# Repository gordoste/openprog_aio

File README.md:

# openprog_aio
All-in-one variant of Alberto Maccioni's wonderful Openprog PIC/AVR programmer (http://openprog.altervista.org/).

## Benefits

For low-voltage programming, the big advantage of this programmer over something like the MPLAB Snap is that it can provide power to the target device, and all of the surrounding circuitry (bypass caps, etc.) is built onto the board. You just plug in a device and program it.

The programmer is also fully capable of high-voltage programming. This is essential if you need to program an older device, and it also means you can use the MCLR pin as an extra I/O, which can be very handy on low-pin-count devices.

This version is aimed at allowing you to get started for the lowest cost and without making your own PCBs. Therefore, the following changes have been made from the original project:

* No adapter boards - just one board, making it cheaper to order from PCB fabrication shops.
* Board is still reasonable size at 158x100mm - approx twice the size of the original project's main board
* Designed to be easily hand-soldered, with 1206 size SMD components. The trickiest thing to solder is the USB socket. You shouldn't need any special equipment if you have clear vision and good lighting - just 0.3mm solder, flux paste and de-soldering braid. NOTE: If you are hand-soldering, it is recommended to use a USB Mini-B socket - see [Part List](#part-list).
* Documentation is on the board, including clear delineation between 5V/3.3V
* Ability to use ZIF sockets for all 20/28 pin sockets if desired.
* PROG button can be used even if device is programmed in low-voltage mode (previously it was attached to RE3/#MCLR)
* ICSP inputs match the MPLAB Snap pinout (different from PICKit).

Please note that the 40-pin Wide DIP sockets have been removed as those devices are rarely used now and took up too much room. If you want to program those devices, you can easily connect the ICSP output to a breadboard.

## Before you start

You need temporary access to a PIC programmer to construct this project. If you don't have a friend with a programmer, the MPLAB Snap is the cheapest commercial option.

## Schematic

The schematic is [here](schematic.pdf).

## Firmware

The original firmware uses unsupported tooling (MCC). I have ported the firmware to MPLAB X and it is available at <https://github.com/gordoste/openprog>. All testing of this board is conducted using this firmware, and testing status of the board/firmware combo can be found at the firmware repository.

## Part List

You can copy and paste [this part list](bom/partlist.txt) into Mouser's BOM tool to order the passive components and semiconductors. In addition to those, you will need the following which are best ordered from AliExpress or similar:
1. IC sockets. You may wish to only populate the sockets you use. Here is a list of all of the sockets:
   | Socket ID | Socket pin count | Device family | Voltage | Device pin count | Can be ZIF? |
   | ----------|------------------|---------------|---------|------------------|-------------|
   | A | 28 | PIC12/16/18 | 3.3V | 28 | Y  |
   | B | 20 | PIC12/16/18 | 3.3V | 8/14/18/20 | Y |
   | C | 28 | PIC24/30/33 | 3.3V | 20/28 | Y |
   | D | 20 | AVR Tiny x61A | 5V | 20 | Y |
   | E | 28 | AVR | 5V | 20/28 | Y |
   | F | 28 | PIC30 | 5V | 18/28 | Y |
   | G | 28 | PIC12/16/18 | 5V | 28 | Y |
   | H | 20 | PIC12/16/18 | 5V | 8/14/16/20 | Y |
   | - | 18 | PIC24-33 | 3.3V | 14/18 | N |
   | - | 8  | SPI Flash | 3.3V | 8 | N |
   | - | 8  | SPI Flash | 5V | 8 | N |
   | - | 8  | uWire Flash | 5V | 8 | N |
   | - | 8  | I2C/UNIO Flash | 5V | 8 | N |
   | - | 8  | PIC 10F20x | 5V | 8 | N |
   | - | 8  | AVR Tiny | 5V | 8 | N |
   | - | 14 | AVR Tiny | 5V | 14 | N |
2. 2.54mm (0.1") pitch pin headers. 3 x 2-pin, 3 x 5-pin, 2 x 4-pin and 1 x 3-pin (all straight). Optionally, you can use a 90-degree header for the 5-pin MPLAB Snap connector.
3. one 6x6mm SMD push button for the PROG button (two if you choose to fit the RESET button)
4. USB socket - either thru-hole Mini-B (I got some from AliExpress which worked fine) or SMD Micro-B (GCT part # USB3076-30-A) (this has fine-pitch pins and is not easy to hand-solder).

## Construction Notes

Download the [ZIP file](https://github.com/gordoste/openprog_aio/releases/download/v1.0b/Openprog_All-in-one_1.0b.zip) containing the PCB gerber files and submit it to your favourite production house.

You can use [this interactive BOM](ibom.html) to assist in placing parts.

Assuming you are hand-soldering, solder the parts in the following order:
1. Back side: Transistors, diodes, resistors, capacitors, regulator
2. Front side: Transistors, diodes, resistors, LEDs, ceramic capacitors, inductor, PIC18F25K50, button(s), electrolytic cap, USB socket, pin headers.

Be careful to only apply a small amount of solder when soldering the USB socket, as it is very easy to create a bridge. Don't panic if you do - turn your soldering iron up a bit hotter than normal, apply a liberal amount of flux and then use desolder braid to try to get rid of __all__ of the solder from the bridged pins. Once it's cleaned up, try again with less solder.

After you've soldered everything, download the HEX file from the [firmware repository](https://github.com/gordoste/openprog) and program it onto the PIC. The marked "MPLAB_SNAP" connector matches the pinout of the Snap (as shown below) - if you're using a PICKit then you will need to utilise jumper wires to connect the programmer.

Assuming you've done everything right, when you plug it into your PC, it should show up as "Open Programmer" and the openprog GUI should be able to talk to it. I recommend using the command line "op" tool with the "-HWtest" option to run through basic checks before actually trying to program anything. See the [openprog webpage](http://openprog.altervista.org/) for more information.

## Usage Notes

### Programming 3.3V I2C EEPROMs

The original project did not provide a socket for this, and I have not yet added one. You can use the SPI@3.3V pin header and connect the following:
|Header pin|Device pin|
|----------|----------|
|GND|GND (4)|
|SCL|SCL (6)|
|MISO|SDA (5)|

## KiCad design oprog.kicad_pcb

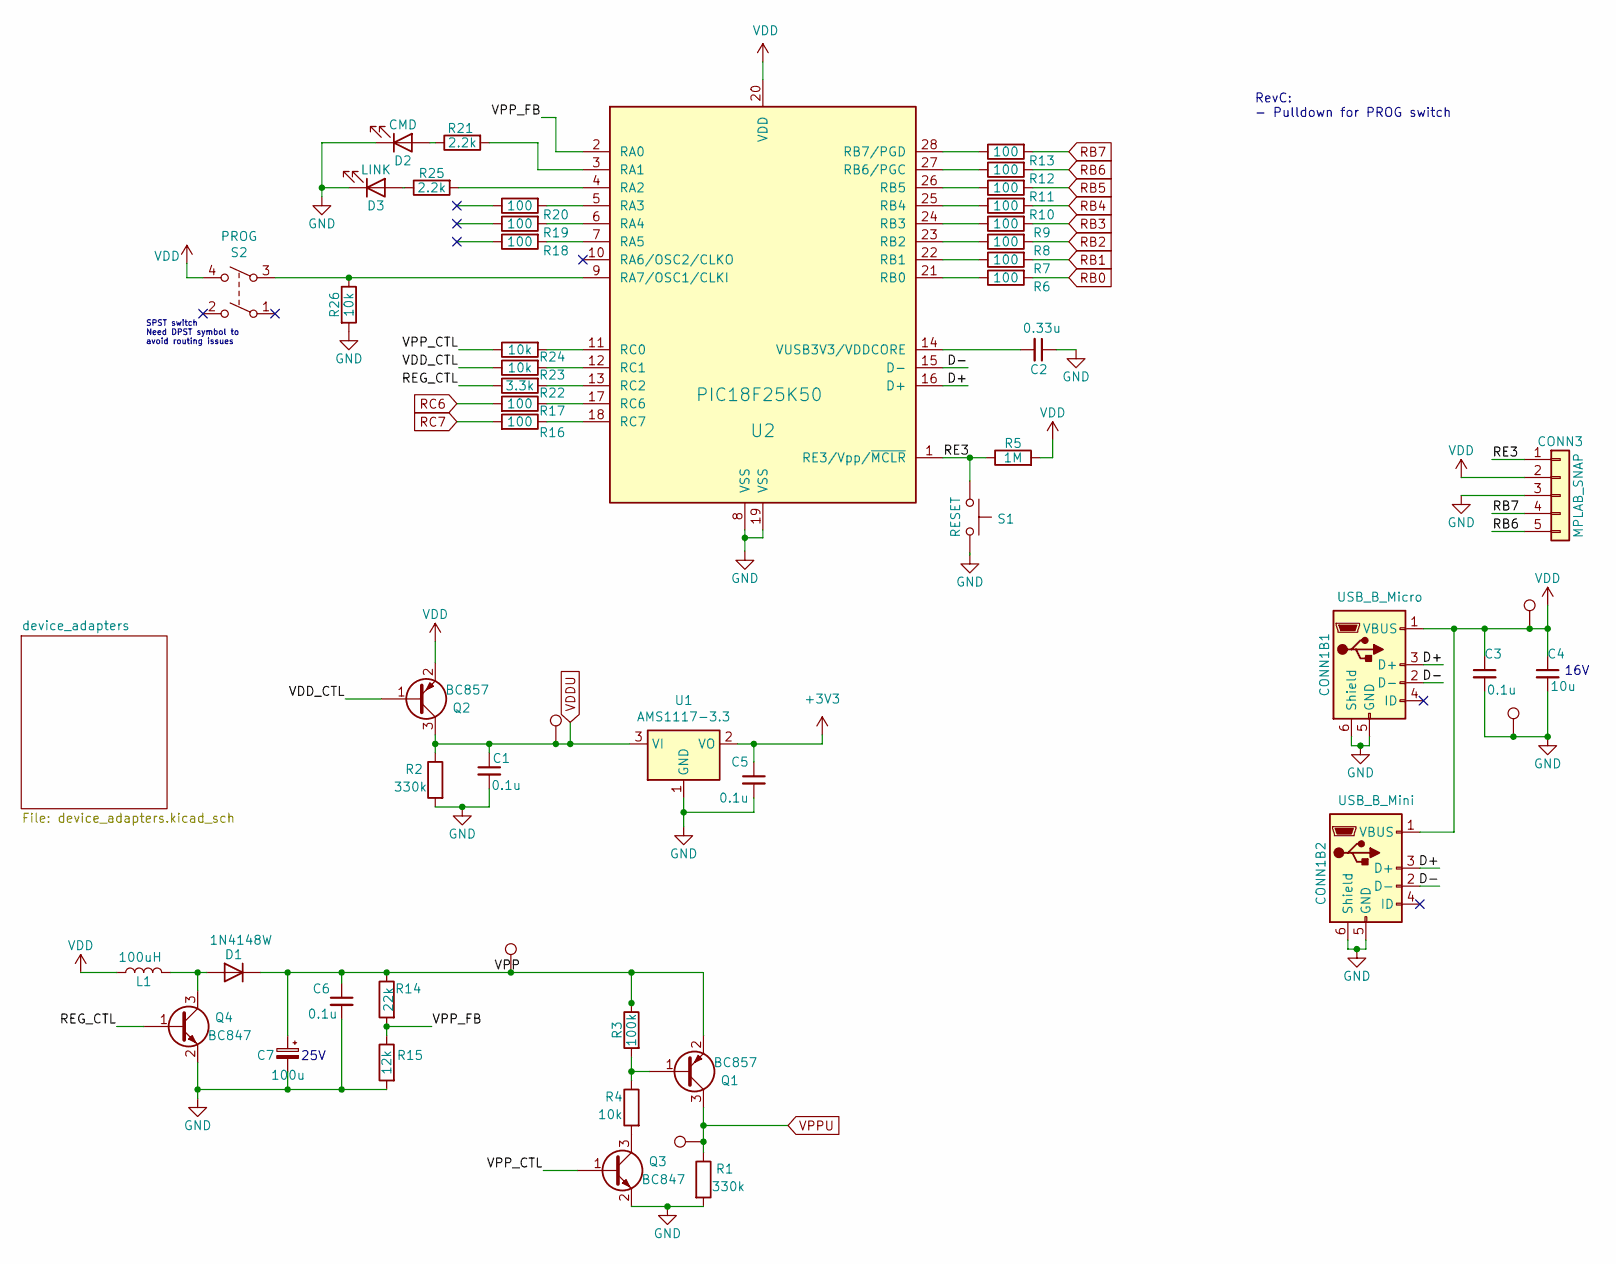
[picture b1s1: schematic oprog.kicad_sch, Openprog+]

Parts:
C1, C3, C5, C6: 0.1u; C_1206_3216Metric_Pad1.33x1.80mm_HandSolder
C2: 0.33u; C_1206_3216Metric_Pad1.33x1.80mm_HandSolder
C4: 10u; C_1206_3216Metric_Pad1.33x1.80mm_HandSolder
C7: 100u; CP_Elec_6.3x5.7
CONN1B1: USB_B_Micro; USB_Micro-B_GCT_USB3076-30-A
CONN1B2: USB_B_Mini; USB_Mini_Type_B_Aliexpress
CONN3: MPLAB_SNAP; PinHeader_1x05_P2.54mm_Vertical
D1: 1N4148W; D_SOD-123
D2: CMD; LED_1206_3216Metric_Pad1.42x1.75mm_HandSolder
D3: LINK; LED_1206_3216Metric_Pad1.42x1.75mm_HandSolder
L1: 100uH; L_1210_3225Metric_Pad1.42x2.65mm_HandSolder
Q1, Q2: BC857; SOT-23
Q3, Q4: BC847; SOT-23
R1, R2: 330k; R_1206_3216Metric_Pad1.30x1.75mm_HandSolder
R3: 100k; R_1206_3216Metric_Pad1.30x1.75mm_HandSolder
R4, R23, R24, R26: 10k; R_1206_3216Metric_Pad1.30x1.75mm_HandSolder
R5: 1M; R_1206_3216Metric_Pad1.30x1.75mm_HandSolder
R6, R7, R8, R9, R10, R11, R12, R13, R16, R17, R18, R19, R20: 100; R_1206_3216Metric_Pad1.30x1.75mm_HandSolder
R14: 22k; R_1206_3216Metric_Pad1.30x1.75mm_HandSolder
R15: 12k; R_1206_3216Metric_Pad1.30x1.75mm_HandSolder
R21, R25: 2.2k; R_1206_3216Metric_Pad1.30x1.75mm_HandSolder
R22: 3.3k; R_1206_3216Metric_Pad1.30x1.75mm_HandSolder
S1: RESET; SW_Push_1P1T_NO_6x6mm_2pads
S2: PROG; SW_Push_1P1T_NO_6x6mm_4pads
TP1: VPPU; TestPoint_THTPad_D1.0mm_Drill0.5mm
TP2: GND; TestPoint_THTPad_D1.0mm_Drill0.5mm
TP3: VDD; TestPoint_THTPad_D1.0mm_Drill0.5mm
TP7: VPP; TestPoint_THTPad_D1.0mm_Drill0.5mm
TP8: VDDU; TestPoint_THTPad_D1.0mm_Drill0.5mm
U1: AMS1117-3.3; SOT-223-3_TabPin2
U2: PIC18F25K50; SOIC-28W_7.5x17.9mm_P1.27mm

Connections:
+3V3: C5.1, U1.2 (VO); also elsewhere on the board
/D+: CONN1B1.3 (D+), CONN1B2.3 (D+), U2.16 (D+)
/D-: CONN1B1.2 (D-), CONN1B2.2 (D-), U2.15 (D-)
/RE3: CONN3.1, R5.1, S1.2, U2.1 (RE3/Vpp/~MCLR)
/REG_CTL: Q4.1 (B), R22.1
/VDD_CTL: Q2.1 (B), R23.1
/VPP: C6.1, C7.1, D1.1 (K), Q1.2 (E), R3.1, R14.1, TP7.1
/VPP_CTL: Q3.1 (B), R24.1
/VPP_FB: R14.2, R15.1, U2.2 (RA0)
GND: C1.2, C2.1, C3.2, C4.2, C5.2, C6.2, C7.2, CONN1B1.5 (GND), CONN1B1.6 (Shield), CONN1B2.5 (GND), CONN1B2.6 (Shield), CONN3.3, D2.1 (K), D3.1 (K), Q3.2 (E), Q4.2 (E), R1.2, R2.2, R15.2, R26.2, S1.1, TP2.1, U1.1 (GND), U2.8 (VSS), U2.19 (VSS); also elsewhere on the board
unnamed: D1.2 (A), L1.1, Q4.3 (C)
unnamed: D2.2 (A), R21.1
unnamed: D3.2 (A), R25.1
unnamed: Q1.1 (B), R3.2, R4.1
unnamed: Q3.3 (C), R4.2
unnamed: R21.2, U2.3 (RA1)
unnamed: R25.2, U2.4 (RA2)
unnamed: R20.2, U2.5 (RA3)
unnamed: R19.2, U2.6 (RA4)
unnamed: R18.2, U2.7 (RA5)
unnamed: R26.1, S2.3, U2.9 (RA7/OSC1/CLKI)
unnamed: R6.1, U2.21 (RB0)
unnamed: R7.1, U2.22 (RB1)
unnamed: R8.1, U2.23 (RB2)
unnamed: R9.1, U2.24 (RB3)
unnamed: R10.1, U2.25 (RB4)
unnamed: R11.1, U2.26 (RB5)
unnamed: R12.1, U2.27 (RB6/PGC)
unnamed: R13.1, U2.28 (RB7/PGD)
unnamed: R24.2, U2.11 (RC0)
unnamed: R23.2, U2.12 (RC1)
unnamed: R22.2, U2.13 (RC2)
unnamed: R17.1, U2.17 (RC6)
unnamed: R16.1, U2.18 (RC7)
unnamed: C2.2, U2.14 (VUSB3V3/VDDCORE)
RB0: R6.2; also elsewhere on the board
RB1: R7.2; also elsewhere on the board
RB2: R8.2
RB3: R9.2; also elsewhere on the board
RB4: R10.2; also elsewhere on the board
RB5: R11.2; also elsewhere on the board
RB6: CONN3.5, R12.2; also elsewhere on the board
RB7: CONN3.4, R13.2; also elsewhere on the board
RC6: R17.2; also elsewhere on the board
RC7: R16.2; also elsewhere on the board
VDD: C3.1, C4.1, CONN1B1.1 (VBUS), CONN1B2.1 (VBUS), CONN3.2, L1.2, Q2.2 (E), R5.2, S2.4, TP3.1, U2.20 (VDD)
VDDU: C1.1, Q2.3 (C), R2.1, TP8.1, U1.3 (VI); also elsewhere on the board
VPPU: Q1.3 (C), R1.1, TP1.1; also elsewhere on the board

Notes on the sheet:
RevC: - Pulldown for PROG switch
SPST switch Need DPST symbol to avoid routing issues
16V
25V

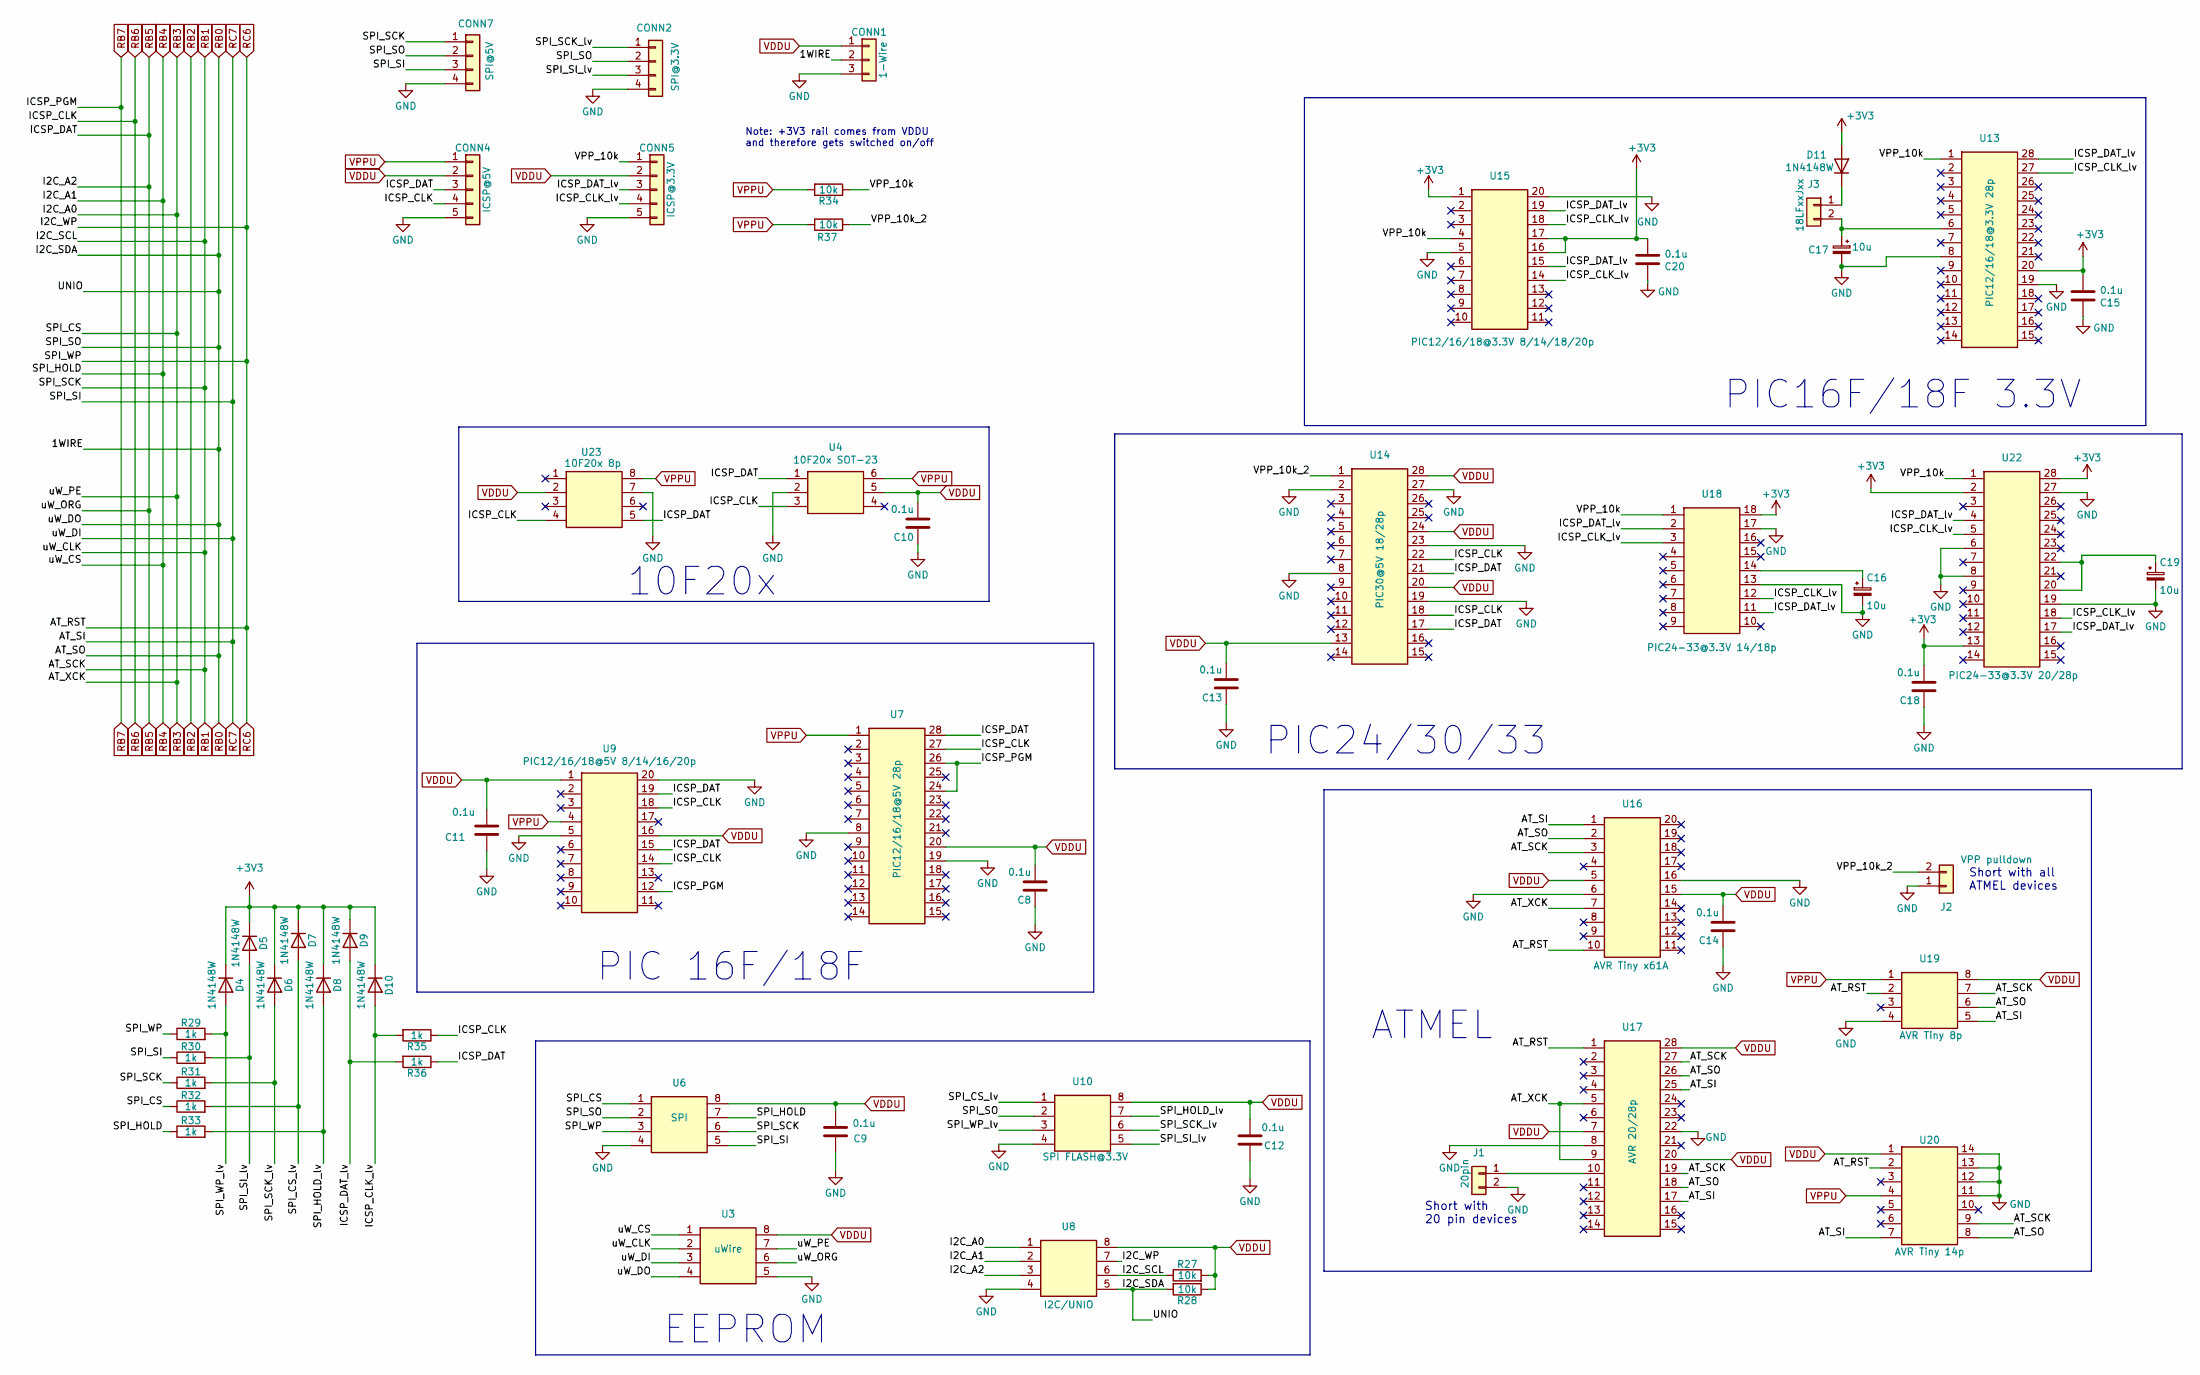
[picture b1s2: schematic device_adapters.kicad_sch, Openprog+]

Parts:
C8, C9, C10, C11, C12, C13, C14, C15, C18, C20: 0.1u; C_1206_3216Metric_Pad1.33x1.80mm_HandSolder
C16, C17, C19: 10u; C_1206_3216Metric_Pad1.33x1.80mm_HandSolder
CONN1: 1-Wire; PinHeader_1x03_P2.54mm_Vertical
CONN2: SPI@3.3V; PinHeader_1x04_P2.54mm_Vertical
CONN4: ICSP@5V; PinHeader_1x05_P2.54mm_Vertical
CONN5: ICSP@3.3V; PinHeader_1x05_P2.54mm_Vertical
CONN7: SPI@5V; PinHeader_1x04_P2.54mm_Vertical
D4, D5, D6, D7, D8, D9, D10, D11: 1N4148W; D_SOD-123
J1: 20pin; PinHeader_1x02_P2.54mm_Vertical
J2: VPP pulldown; PinHeader_1x02_P2.54mm_Vertical
J3: 18LFxxJxx; PinHeader_1x02_P2.54mm_Vertical
R27, R28, R34, R37: 10k; R_1206_3216Metric_Pad1.30x1.75mm_HandSolder
R29, R30, R31, R32, R33, R35, R36: 1k; R_1206_3216Metric_Pad1.30x1.75mm_HandSolder
U3: uWire; DIP-8_W7.62mm_Socket
U4: 10F20x SOT-23; SOT-23-6_Handsoldering
U6: SPI; DIP-8_W7.62mm_Socket
U7: PIC12/16/18@5V 28p; ZIFSocket_28p_W7.62mm
U8: I2C/UNIO; DIP-8_W7.62mm_Socket
U9: PIC12/16/18@5V 8/14/16/20p; ZIFSocket_20p_W7.62mm
U10: SPI FLASH@3.3V; DIP-8_W7.62mm_Socket
U13: PIC12/16/18@3.3V 28p; ZIFSocket_28p_W7.62mm
U14: PIC30@5V 18/28p; ZIFSocket_28p_W7.62mm
U15: PIC12/16/18@3.3V 8/14/18/20p; ZIFSocket_20p_W7.62mm
U16: AVR Tiny x61A; ZIFSocket_20p_W7.62mm
U17: AVR 20/28p; ZIFSocket_28p_W7.62mm
U18: PIC24-33@3.3V 14/18p; DIP-18_W7.62mm_Socket
U19: AVR Tiny 8p; DIP-8_W7.62mm_Socket
U20: AVR Tiny 14p; DIP-14_W7.62mm_Socket
U22: PIC24-33@3.3V 20/28p; ZIFSocket_28p_W7.62mm
U23: 10F20x 8p; DIP-8_W7.62mm_Socket

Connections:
+3V3: C15.2, C18.2, C20.2, D4.1 (K), D5.1 (K), D6.1 (K), D7.1 (K), D8.1 (K), D9.1 (K), D10.1 (K), D11.2 (A), U13.20, U15.1, U15.16, U15.17, U18.18, U22.2, U22.13, U22.28; also elsewhere on the board
/device_adapters/ICSP_CLK_lv: CONN5.4, D10.2 (A), R35.2, U13.27, U15.14, U15.18, U18.3, U18.12, U22.5, U22.18
/device_adapters/ICSP_DAT_lv: CONN5.3, D9.2 (A), R36.2, U13.28, U15.15, U15.19, U18.2, U18.11, U22.4, U22.17
/device_adapters/SPI_CS_lv: D7.2 (A), R32.2, U10.1
/device_adapters/SPI_HOLD_lv: D8.2 (A), R33.2, U10.7
/device_adapters/SPI_SCK_lv: CONN2.1, D6.2 (A), R31.2, U10.6
/device_adapters/SPI_SI_lv: CONN2.3, D5.2 (A), R30.2, U10.5
/device_adapters/SPI_WP_lv: D4.2 (A), R29.2, U10.3
/device_adapters/VPP_10k: CONN5.1, R34.1, U13.1, U15.4, U18.1, U22.1
/device_adapters/VPP_10k_2: J2.2, R37.2, U14.1
GND: C8.1, C9.1, C10.1, C11.1, C12.1, C13.1, C14.1, C15.1, C16.2, C17.2, C18.1, C19.2, C20.1, CONN1.3, CONN2.4, CONN4.5, CONN5.5, CONN7.4, J1.2, J2.1, U3.5, U4.2, U6.4, U7.8, U7.19, U8.4, U9.5, U9.20, U10.4, U13.8, U13.19, U14.2, U14.8, U14.19, U14.23, U14.27, U15.5, U15.20, U16.6, U16.16, U17.8, U17.22, U18.13, U18.17, U19.4, U20.11, U20.12, U20.13, U20.14, U22.6, U22.8, U22.19, U22.27, U23.7; also elsewhere on the board
unnamed: C16.1, U18.14
unnamed: C19.1, U22.20, U22.22
unnamed: D11.1 (K), J3.1
unnamed: J1.1, U17.10
unnamed: C17.1, J3.2, U13.6
RB0: CONN1.2, CONN2.2, CONN7.2, R28.2, U3.4, U6.2, U8.5, U10.2, U16.2, U17.18, U17.26, U19.6, U20.8; also elsewhere on the board
RB1: CONN7.1, R27.1, R31.1, U3.2, U6.6, U8.6, U16.3, U17.19, U17.27, U19.7, U20.9; also elsewhere on the board
RB3: R32.1, U3.7, U6.1, U8.1, U16.7, U17.5, U17.9; also elsewhere on the board
RB4: R33.1, U3.1, U6.7, U8.2; also elsewhere on the board
RB5: CONN4.3, R36.1, U3.6, U4.1, U7.28, U8.3, U9.15, U9.19, U14.17, U14.21, U23.5; also elsewhere on the board
RB6: CONN4.4, R35.1, U4.3, U7.27, U9.14, U9.18, U14.18, U14.22, U23.4; also elsewhere on the board
RB7: U7.24, U7.26, U9.12; also elsewhere on the board
RC6: R29.1, U6.3, U8.7, U16.10, U17.1, U19.2, U20.2; also elsewhere on the board
RC7: CONN7.3, R30.1, U3.3, U6.5, U16.1, U17.17, U17.25, U19.5, U20.7; also elsewhere on the board
VDDU: C8.2, C9.2, C10.2, C11.2, C12.2, C13.2, C14.2, CONN1.1, CONN4.2, CONN5.2, R27.2, R28.1, U3.8, U4.5, U6.8, U7.20, U8.8, U9.1, U9.16, U10.8, U14.13, U14.20, U14.24, U14.28, U16.5, U16.15, U17.7, U17.20, U17.28, U19.8, U20.1, U23.2; also elsewhere on the board
VPPU: CONN4.1, R34.2, R37.1, U4.6, U7.1, U9.4, U19.1, U20.4, U23.8; also elsewhere on the board

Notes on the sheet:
Short with all ATMEL devices
Note: +3V3 rail comes from VDDU and therefore gets switched on/off
PIC16F/18F 3.3V
10F20x
EEPROM
Short with 20 pin devices
PIC24/30/33
PIC 16F/18F
ATMEL

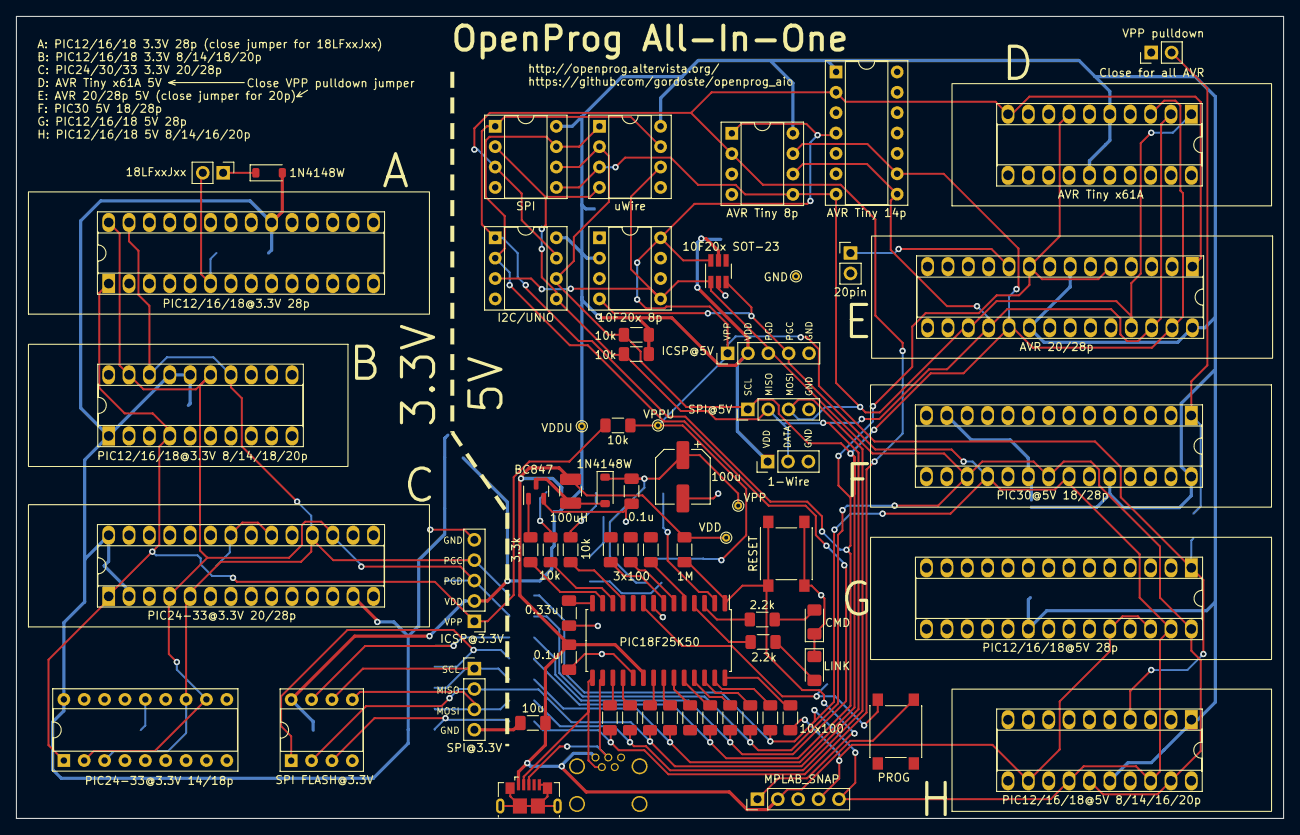
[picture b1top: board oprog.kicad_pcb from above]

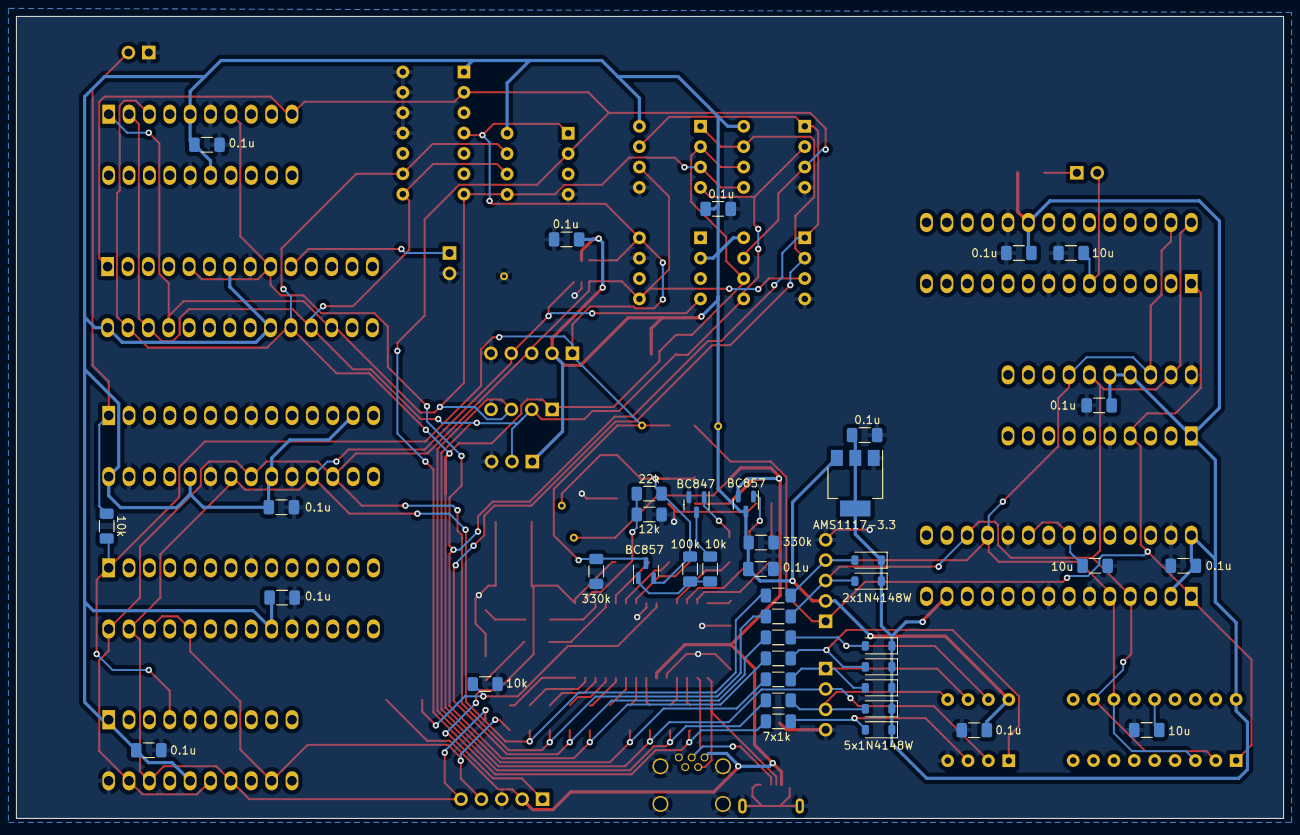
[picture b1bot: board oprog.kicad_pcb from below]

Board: 2 copper layers, 158.0 x 100.0 mm, 110 parts (41 on the bottom side), 61 nets.

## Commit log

2023-10-28 Initial release - v1.0b
2023-10-28 Add license and readme
2023-10-28 Ignore lock files
2023-10-28 Populate README
2023-10-28 Add BOM
2023-10-28 Add BOM to README
2023-10-28 Remove old BOM
2023-10-28 typo
2023-10-29 Add part list
2023-10-31 Add schematic
2023-10-31 Add schematic to README
2023-11-09 Update photo
2023-11-09 Remove testing spreadsheet
2023-11-09 Update README with more details
2023-11-10 Move board photo to top, add photo of Snap
2023-11-10 Add board render
2023-11-11 Explain how to program 3.3V I2C EEPROMs
